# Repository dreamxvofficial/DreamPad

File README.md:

# DreamPad
### DreamPad
A custom little control pad that I made for my laptop 

It is a custom USB control pad I made because I wanted to have quick access to keyboard shortcuts and websites, and my most used laptop shortcuts as physical buttons.

It has 9 buttons, an OLED Display and a Rotatory Encoder. The first 3 buttons are Cut, Copy and Paste. The other 6 can be set to wbsites that I often use.

---

## Why I Made This

### I use my laptop a lot for coding and working on hardware projects, and i keep using the same shortcuts and website again and again(*also it was a mission in Stardance... LOL*)

So I thought, why not just make a small device for them?(**for mission :D**)

---

## Button Layout 

| Position | Function |
|---  |---|
| 0,0 | Cut |
| 0,1 | Copy |
| 0,2 | Paste |
| 1,0 | Link 1 |
| 1,1 | Link 2 |
| 1,2 | Link 3 |
| 2,0 | Link 4 |
| 2,1 | Link 5 |
| 2,2 | Link 6 |

The 6 links can be changed in the Firmware.

For example, I can set them to:

```text
YouTube
Hack Club
GitHub
Slack
ChatGPT
My own website
```
## Parts (*that i got for mission*)
| Part | What I use it for |
|---|---|
| XIAO RP2040 | Main controller |
| 9 × Switches | Buttons |
| 9 × Diodes | Key matrix |
| OLED | Display |
| Rotary Encoder | Volume |
| PCB | Connecting everything |
| 3D Printed Case | Enclosure |

---

## Schematic 

I started the project by making schematic in KiCad.

This is where I worked out how the 9 buttons, OLED, rotary encoder and XIAO RP2040 would all connect.

---

## PCB

Once the schematic was working, I moved on to the PCB.

I placed all the components and routed the connections on the board.

---

## PCB 3D View

I used the 3D view in KiCad to check how the components would sit on the board.

This also helped me catch placement problems before making the enclosure.

---

## CAD

After the PCB, I made the case in Fusion 360.

I designed the case around the actual PCB and components so everything would fit inside.

---
## CAD + PCB

I then put the PCB and the case together in Fusion 360 to check the fit.

This was useful for checking things like the button positions, OLED, rotary encoder and the space inside the case.

---

## Firmware

The firmware is written for the XIAO RP2040 using Antigravity IDE.

The DreamPad connects directly to my laptop using the USB port on the XIAO.

The firmware handles:

- Cut
- Copy
- Paste
- 6 custom links
- OLED
- Rotary encoder
- Volume up/down
- Mute

The links are just variables in the code, so I can change them whenever I want.

---

## What I learned

This project made me learn a lot of things I hadn't really worked with before.

I got to work with KiCad, PCB routing, key matrices, rotary encoders, OLEDs, the RP2040 and Fusion 360.

The CAD part was also pretty interesting because I had to make the case around the actual PCB instead of just designing something that looked good.

---

## Made by

**DreamXV**

**DreamPad** — something I built because I wanted my own physical shortcuts instead of always reaching for the keyboard.

> **And ALSO FOR THE MISSION :D**

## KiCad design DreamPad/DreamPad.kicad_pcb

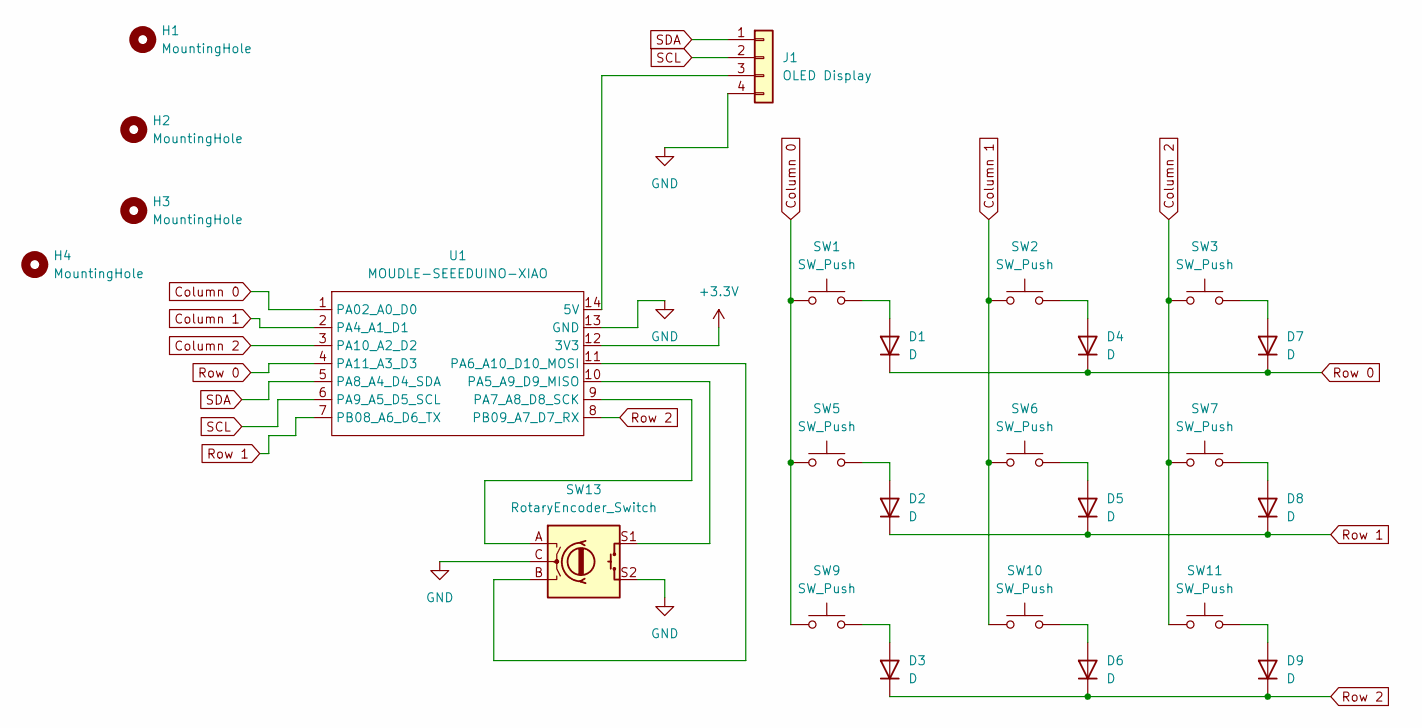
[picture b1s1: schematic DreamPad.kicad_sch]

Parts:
D1, D2, D3, D4, D5, D6, D7, D8, D9: D; D_DO-35_SOD27_P7.62mm_Horizontal
H1, H2, H3, H4: MountingHole; MountingHole_3.2mm_M3
J1: OLED Display; PinSocket_1x04_P2.54mm_Vertical
SW1, SW2, SW3, SW5, SW6, SW7, SW9, SW10, SW11: SW_Push; SW_Cherry_MX_1.00u_PCB
SW13: RotaryEncoder_Switch; RotaryEncoder_Alps_EC11E-Switch_Vertical_H20mm
U1: MOUDLE-SEEEDUINO-XIAO; XIAO-Generic-Hybrid-14P-2.54-21X17.8MM

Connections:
+3.3V: U1.12 (3V3)
Column 0: SW1.1, SW5.1, SW9.1, U1.1 (PA02_A0_D0)
Column 1: SW2.1, SW6.1, SW10.1, U1.2 (PA4_A1_D1)
Column 2: SW3.1, SW7.1, SW11.1, U1.3 (PA10_A2_D2)
GND: J1.4, SW13.C, SW13.S2, U1.13 (GND)
unnamed: D1.2 (A), SW1.2
unnamed: D2.2 (A), SW5.2
unnamed: D3.2 (A), SW9.2
unnamed: D4.2 (A), SW2.2
unnamed: D5.2 (A), SW6.2
unnamed: D6.2 (A), SW10.2
unnamed: D7.2 (A), SW3.2
unnamed: D8.2 (A), SW7.2
unnamed: D9.2 (A), SW11.2
unnamed: J1.3, U1.14 (5V)
unnamed: SW13.S1, U1.10 (PA5_A9_D9_MISO)
unnamed: SW13.B, U1.11 (PA6_A10_D10_MOSI)
unnamed: SW13.A, U1.9 (PA7_A8_D8_SCK)
Row 0: D1.1 (K), D4.1 (K), D7.1 (K), U1.4 (PA11_A3_D3)
Row 1: D2.1 (K), D5.1 (K), D8.1 (K), U1.7 (PB08_A6_D6_TX)
Row 2: D3.1 (K), D6.1 (K), D9.1 (K), U1.8 (PB09_A7_D7_RX)
SCL: J1.2, U1.6 (PA9_A5_D5_SCL)
SDA: J1.1, U1.5 (PA8_A4_D4_SDA)

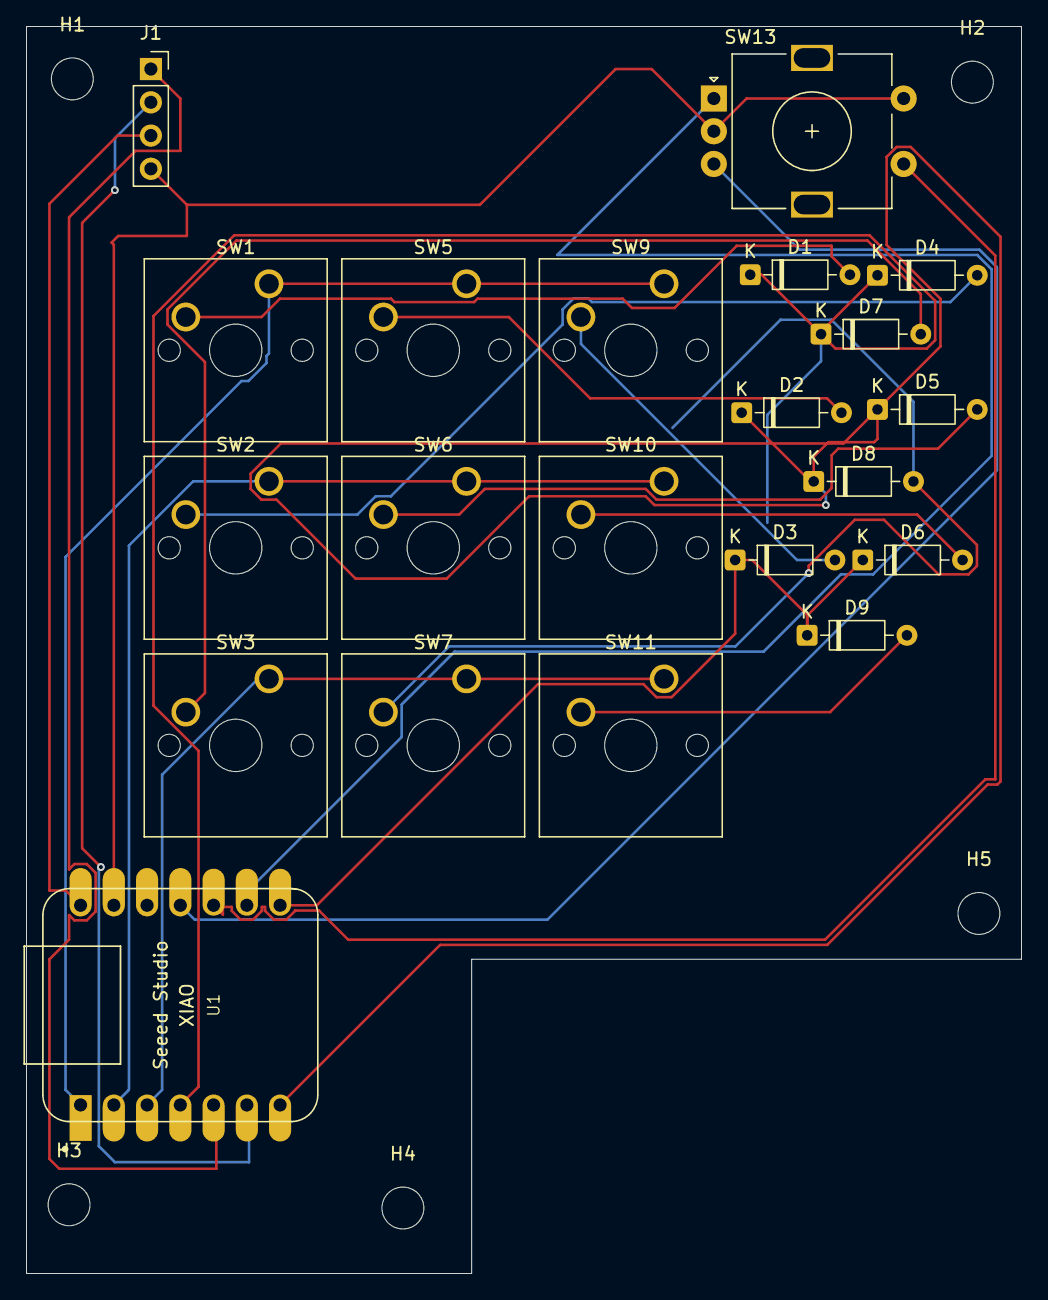
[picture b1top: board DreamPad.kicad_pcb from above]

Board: 2 copper layers, 76.0 x 95.2 mm, 26 parts (0 on the bottom side), 22 nets.

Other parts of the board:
H5: MountingHole; MountingHole_3.2mm_M3
